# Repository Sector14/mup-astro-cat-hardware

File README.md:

# MUP Astro CAT

The MUP Astro CAT is an auto GPIO configuring add-on board for the
Raspberry PI 3 which provides additional hardware interfaces to 
communicate and control a Meade Autostar, Moonlite focuser and
temperature sensors.

This repository contains the hardware project files needed to build 
the MUP Astro CAT. Firmware and the INDI driver is available in a separte
repo:

  https://github.com/Sector14/mup-astro-cat

Please refer to the additional documentation in the docs/ directory for
information on port pinouts for cables and hardware testing notes.

CAT refers to the Schmidt-Cassagrain telescope (CAT for short) this board will
be attached to. After naming it CAT I considered the recursive "CAP" which
would stand for "CAP Attached on Pi" since this project doesn't quite meet
the "Hat" spec, a cap is not a hat! but that means renaming things so CAT it is.

# Directories

  * control_cat - Kicad 4 project incl schematic/pcb layout for the MUP Astro Cat. (CERN)
  * docs        - Documentation and 3rd party datasheets
  * gerber      - Exported gerber files for re-ordering PCBs

# Intended Purpose

Use a raspberry pi and additional interface board to control the 
following devices:

  * SXVR-H9
  * LodeStar
  * Filter Wheel
  * LX90 Handset
  * Moonlite Focuser
  * Illuminated Reticle (v2?)
  * Temp Sensor

The SXVR-H9, LodeStar (excl ST4 guide port) and Filter Wheel simply 
connect as USB devices to the Pi. 

The LX90 Handset uses a RS232 connection via RJ22 to the PI.

Moonlite focuser controlled via GPIO to a unipolar stepper
motor controller that will handle signal timing. Ensures any 
jitter/pauses from pi due to non realtime OS won't impact
motor control.

ST4 port from APM is not implemented, it might be added in a future
revision via i2c bus however as the LX90 supports pulse commands
over serial, it may not be needed.

# Library Setup

In addition to the libraries, modules and models that ship with Kicad,
this project also uses the MUP Kicad Library for additional parts and
an optional 3rd party 3D model library.

## Eeschema

If you receive a "The following libraries were not found:" message when
opening the schematic then you do not have the MUPS Kicad library available.
Kicad will use a cached copy of the library so this step is optional, but 
if you wish to make changes you should clone the repo:

  https://github.com/Sector14/mup-kicad-library

and add its location "Preferences/Component Libraries" as a user defined 
search path in the "parts library editor".  Then close and re-open Eeschema
and all the schematic symbols should now be found.

## Footprints

The above repo also contains footprint files for PCBNew in the modules/
directory and 3d models (where applicable). PCBNew will need each modules/\*.pretty
directory adding to the global library, or if you prefer, the project specific 
libraries.

To do so, open PCBNew, "Preferences/Footprints Libraries Manager", then 
"Append with Wizard" and select each ".pretty" directory and click Next, then
select whether to add the footprint to the global or project library.

Note: Some footprints are unchanged Kicad footprints that have only been
saved to the MUPS library in order to associate a 3d model with the footprint.
If the official Kicad library ever adds the missing models, the parts will
likely be removed from this repo.

## 3d Models

Some parts include a reference to models from the GPL'd 3d library by "kcswalter".
These are optional models and not included in the MUPS Kicad library.

If you checkout the walter repo from

  git://smisioto.eu/kicad_libs.git 

You can have Kicad use these models during 3d preview mode
by adding a new env variable in PCBNew "Preferences/Configure Paths" 
called WALTER_KI3DMOD and with the path set to the 
<walter repo checkout path>/modules/packages3d/ directory. 

Any footprints in the MUPS library that has the 3d model path prefixed 
with {WALTER_KI3DMOD}/walter/ will then use the appropriate 3D model.
The same will apply to {MUPS_KI3DMOD}/mups/ although at this time I've
yet to create any custom 3D models and find it unlikely I will

# Gerber Export

For Ordering PCBs from dirtypcbs.com

For "plotting":-

  * "Gerber" format is selected.
  * Select Layers F.Cu, B.Cu, F.SilkS, B.Mask, F.Mask, Edge.Cuts
  * Select Options:
   * Plot footprint values
   * Plot footprint references
   * Exclude PCB edge layer from other layers
  * Select Gerber Options:
   * User Protel filename extensions

For Drill file:

  * Units Inches
  * Zeros Format, Suppress leading zeros
  * Drill Map File Format (not used)
  * Drill File Options:
   * Minimal header
   * Merge PTH and NPTH holes into one file
  * Drill origin, Absolute

After export, rename the edge cuts "gm1" extension to "gml" prior
to uploading zip to dirtypcbs.com.

# Future Revision

Selecting surface 1206 style footprint for C8, the 100uF bypass capacitor 
for the DRV8805 was a little costly due to needing higher than 12V. An 
SMD electrolytic would prove significantly cheaper £0.27 vs £2.46
and with a greater voltage margin and not require that much additional 
space for a radial footprint. Lapse in judgement to be corrected on a 
future revision.

The power supply could be reduced in size with a more carefully
selected inductor. Having never laid out a SMPS however, I decided
to stick to the recommended layout and inductors based on the
TI regulator used. Further experimentation will be done prior to
revision 2 along with a change to SMD electrolytics and diodes.

A surface mounting socket to mate the CAT to the pi would be a better
choice as it allows an extended pin leg header to be mounted to the
pi and then the CAT mounted on top. This works out cheaper than the
elevated sockets.

Signal lines all need test point locations making available.

Switch 4p4c and 6p6c connector layout to socket mounting 
to allow panel mount option or in the case of a direct wiring, a
smaller connector area.

USB ideally should also be panel mount but desoldering the PI's
dual sockets is something I'd prefer to avoid.

ST3232 switch to soic version.

Add pin labels to silkscreen for temp port etc current broken square for
ground is too hard to see once a pin header is soldered in place.

Add a via behind the regulator to connect ground planes for better
thermal relief.

HAT specs for back-powering via 5V GPIO header pin requires addition
of an ideal 'safety' diode see [design guide](https://github.com/raspberrypi/hats/blob/master/designguide.md)

# Reference

  * https://github.com/raspberrypi/hats
  * https://github.com/raspberrypi/hats/blob/master/designguide.md
  * https://github.com/xesscorp/RPi_Hat_Template
  * http://www.briandorey.com/post/Raspberry-Pi-3-UART-Boot-Overlay-Part-Two

# Copyright

Copyright Gary Preston 2016.

This documentation describes Open Hardware and is licensed under the
CERN OHL v. 1.2.

You may redistribute and modify this documentation under the terms of the
CERN OHL v.1.2. (http://ohwr.org/cernohl). This documentation is distributed
WITHOUT ANY EXPRESS OR IMPLIED WARRANTY, INCLUDING OF
MERCHANTABILITY, SATISFACTORY QUALITY AND FITNESS FOR A
PARTICULAR PURPOSE. Please see the CERN OHL v.1.2 for applicable
conditions

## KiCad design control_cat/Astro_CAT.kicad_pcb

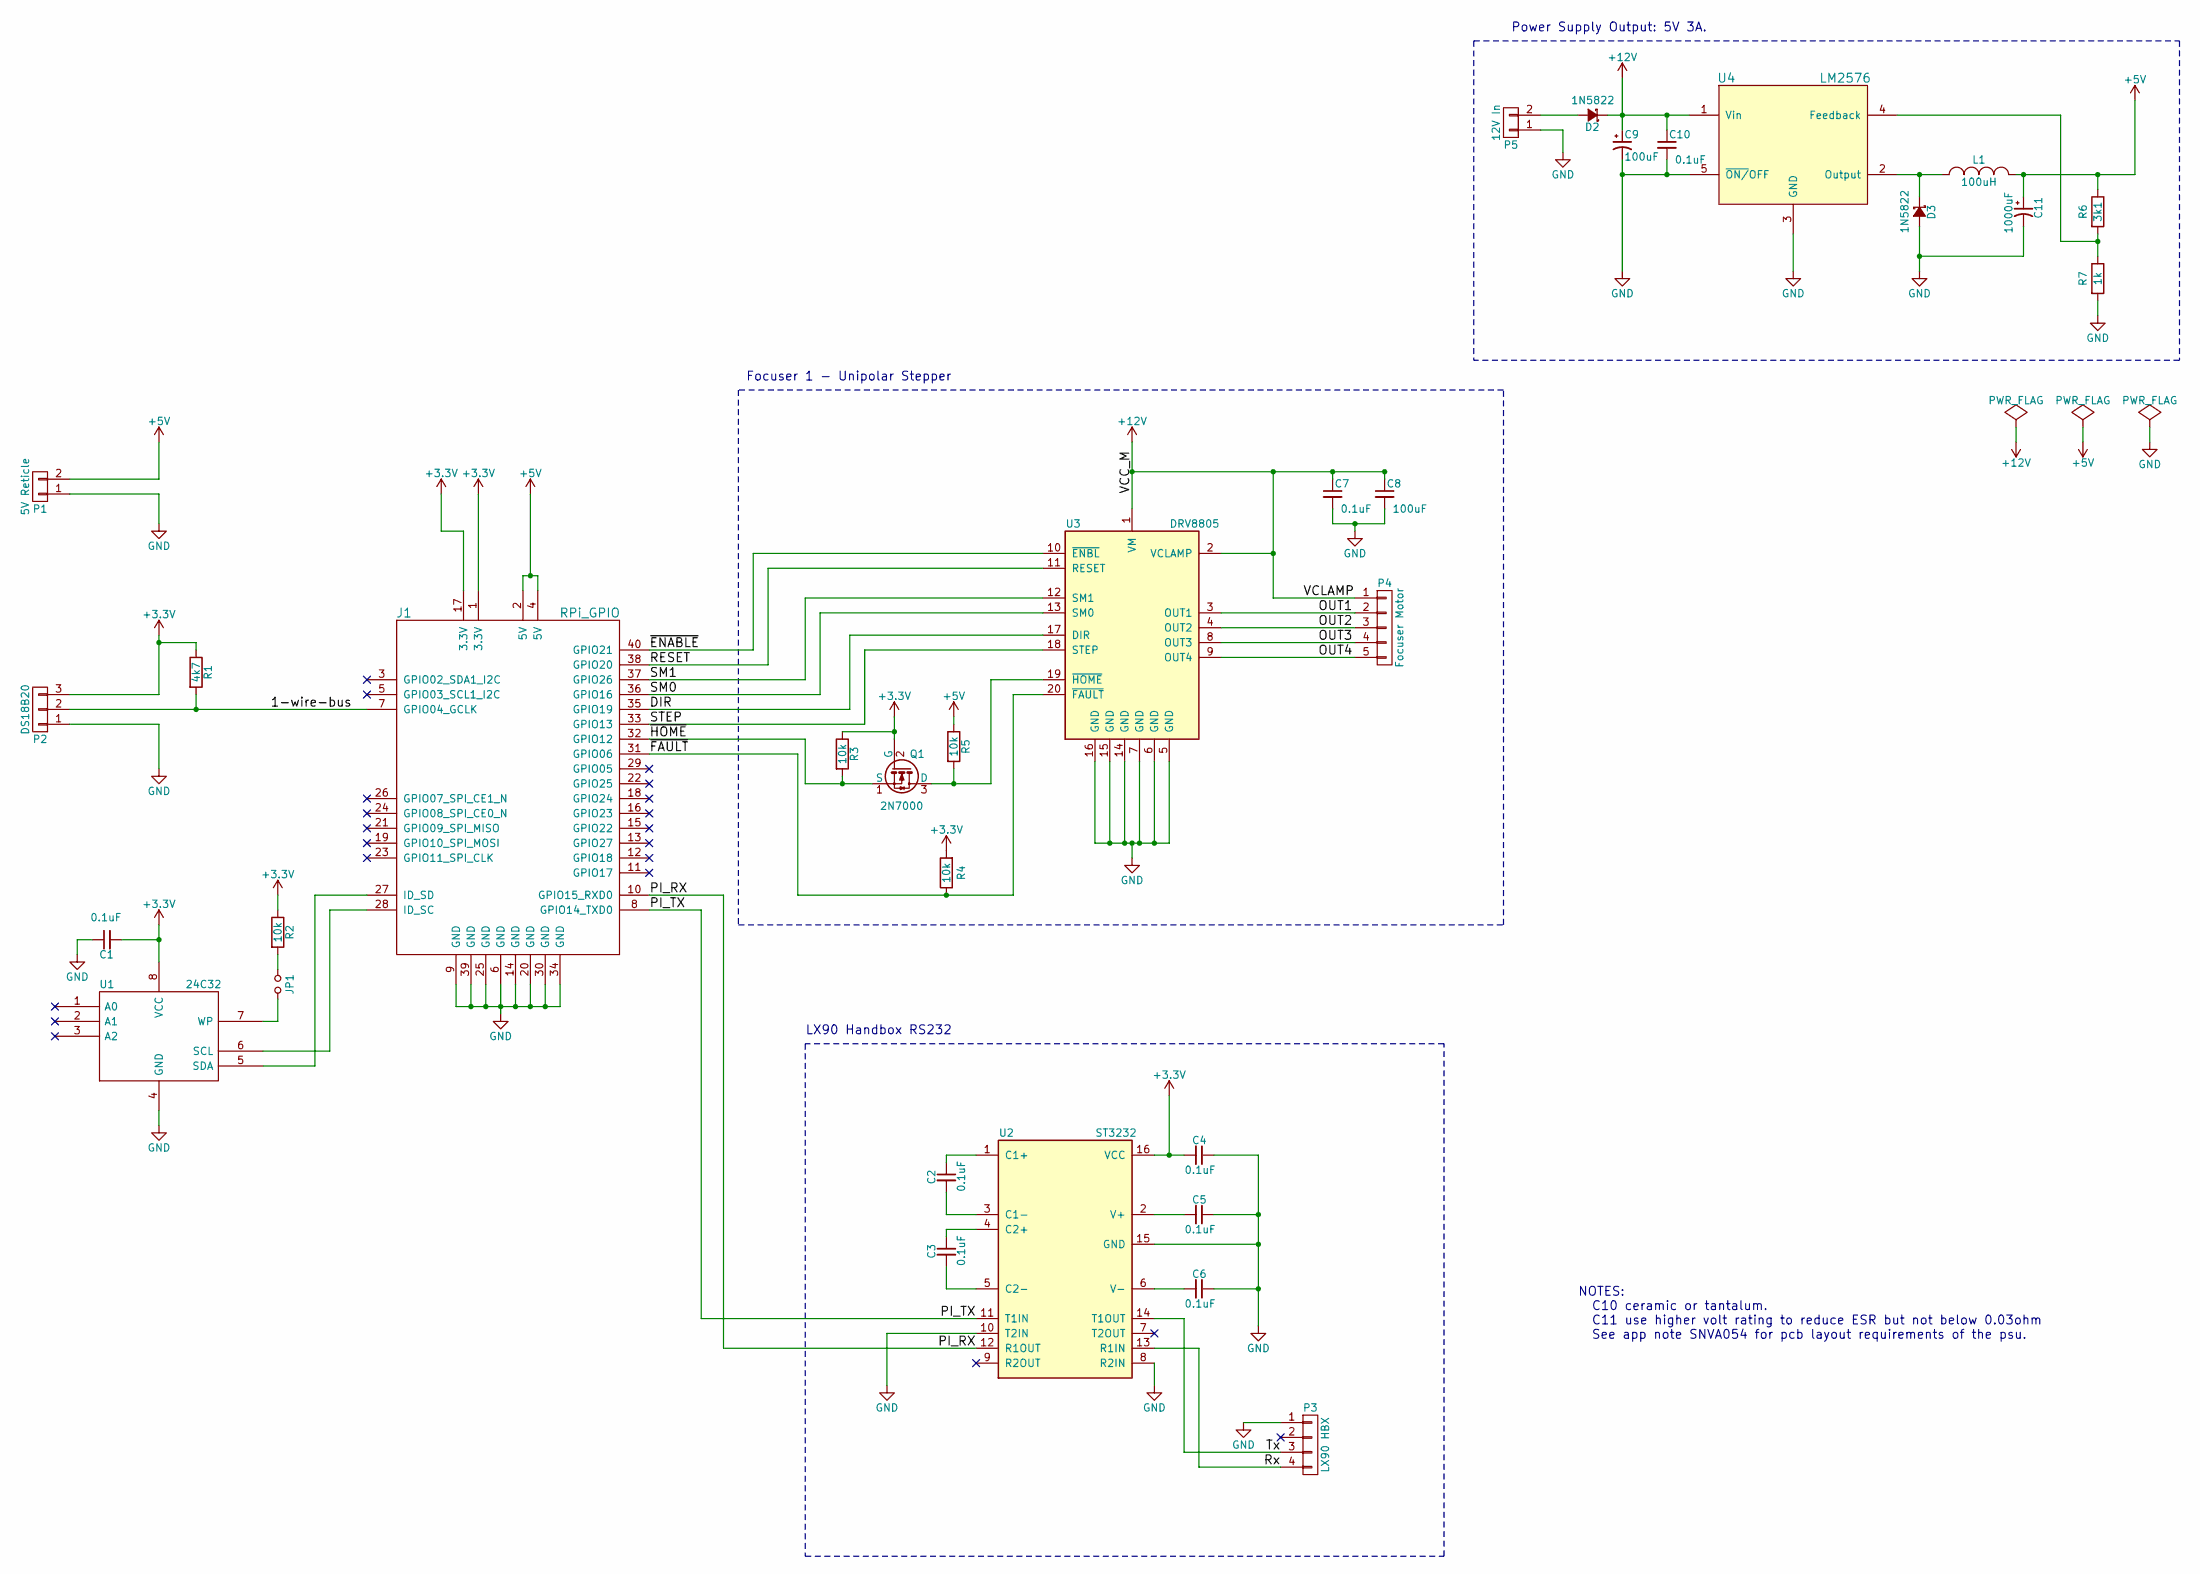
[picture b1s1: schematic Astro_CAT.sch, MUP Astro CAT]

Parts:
C1, C2, C3, C4, C5, C6, C7, C10: 0.1uF; C_1206_HandSoldering
C8: 100uF; C_1206_HandSoldering
C9: 100uF; C_Radial_D6.3_L11.2_P2.5
C11: 1000uF; C_Radial_D10_L16_P5
D2, D3: 1N5822; Diode_DO-201AD_Horizontal_RM15
J1: RPi_GPIO; PI_Pin_Header_Straight_2x20
JP1: Jumper_NO_Small; PINHEAD1-2
L1: 100uH; Choke_Toroid_8x16mm_Vertical
P1: 5V Reticle; Pin_Header_Straight_1x02
P2: DS18B20; Pin_Header_Straight_1x03
P3: LX90 HBX; 4P4C
P4: Focuser Motor; 6P6C
P5: 12V In; Terminal_Block_5mm_2
Q1: 2N7000; TO-92_Inline_Wide
R1: 4k7; R_1206_HandSoldering
R2, R3, R4, R5: 10k; R_1206_HandSoldering
R6: 3k1; R_1206_HandSoldering
R7: 1k; R_1206_HandSoldering
U1: 24C32; SOIC-8_3.9x4.9mm_Pitch1.27mm
U2: ST3232; DIP-16_W7.62mm
U3: DRV8805; SOIC-20_7.5x12.8mm_Pitch1.27mm
U4: LM2576; Pentawatt_Neutral_Staggered_Verical_TO220-5-T05D

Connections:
+3V3: C1.2, C4.2, J1.1 (3.3V), J1.17 (3.3V), P2.3, Q1.2 (G), R1.1, R2.1, R3.1, R4.2, U1.8 (VCC), U2.16 (VCC)
+5V: C11.1, J1.2 (5V), J1.4 (5V), L1.2, P1.2, R5.1, R6.1
+12V: C7.1, C8.1, C9.1, C10.1, D2.1 (K), P4.1, U3.1 (VM), U3.2 (VCLAMP), U4.1 (Vin)
/1-wire-bus: J1.7 (GPIO04_GCLK), P2.2, R1.2
/DIR: J1.35 (GPIO19), U3.17 (DIR)
/OUT1: P4.2, U3.3 (OUT1)
/OUT2: P4.3, U3.4 (OUT2)
/OUT3: P4.4, U3.8 (OUT3)
/OUT4: P4.5, U3.9 (OUT4)
/PI_RX: J1.10 (GPIO15_RXD0), U2.12 (R1OUT)
/PI_TX: J1.8 (GPIO14_TXD0), U2.11 (T1IN)
/RESET: J1.38 (GPIO20), U3.11 (RESET)
/Rx: P3.4, U2.13 (R1IN)
/SM0: J1.36 (GPIO16), U3.13 (SM0)
/SM1: J1.37 (GPIO26), U3.12 (SM1)
/STEP: J1.33 (GPIO13), U3.18 (STEP)
/Tx: P3.3, U2.14 (T1OUT)
/~ENABLE: J1.40 (GPIO21), U3.10 (~ENBL)
/~FAULT: J1.31 (GPIO06), R4.1, U3.20 (~FAULT)
/~HOME: J1.32 (GPIO12), Q1.1 (S), R3.2
GND: C1.1, C4.1, C5.1, C6.1, C7.2, C8.2, C9.2, C10.2, C11.2, D3.2 (A), J1.6 (GND), J1.9 (GND), J1.14 (GND), J1.20 (GND), J1.25 (GND), J1.30 (GND), J1.34 (GND), J1.39 (GND), P1.1, P2.1, P3.1, P5.1, R7.2, U1.4 (GND), U2.8 (R2IN), U2.10 (T2IN), U2.15 (GND), U3.5 (GND), U3.6 (GND), U3.7 (GND), U3.14 (GND), U3.15 (GND), U3.16 (GND), U4.3 (GND), U4.5 (~ON/~OFF)
unnamed: C2.1, U2.1 (C1+)
unnamed: C2.2, U2.3 (C1-)
unnamed: C3.1, U2.4 (C2+)
unnamed: C3.2, U2.5 (C2-)
unnamed: C5.2, U2.2 (V+)
unnamed: C6.2, U2.6 (V-)
unnamed: D2.2 (A), P5.2
unnamed: D3.1 (K), L1.1, U4.2 (Output)
unnamed: J1.27 (ID_SD), U1.5 (SDA)
unnamed: J1.28 (ID_SC), U1.6 (SCL)
unnamed: JP1.1, R2.2
unnamed: JP1.2, U1.7 (WP)
unnamed: Q1.3 (D), R5.2, U3.19 (~HOME)
unnamed: R6.2, R7.1, U4.4 (Feedback)

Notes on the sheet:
LX90 Handbox RS232
Focuser 1 - Unipolar Stepper
Power Supply Output: 5V 3A.
NOTES: C10 ceramic or tantalum. C11 use higher volt rating to reduce ESR but not below 0.03ohm See app note SNVA054 for pcb layout requirements of the psu.

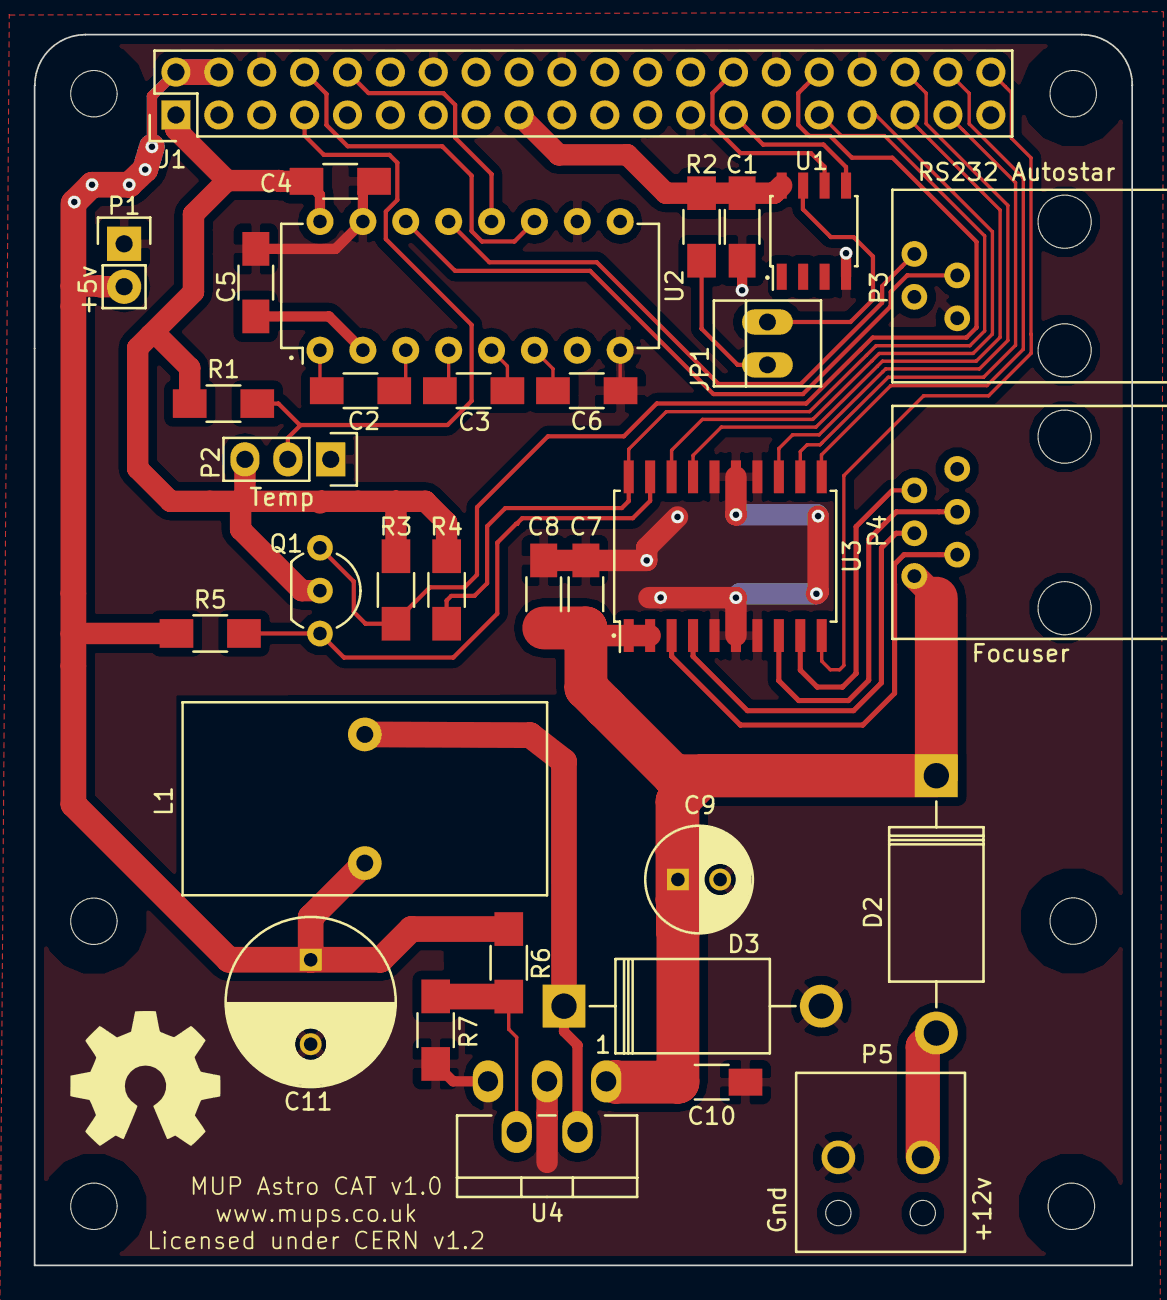
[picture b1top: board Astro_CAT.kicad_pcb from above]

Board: 2 copper layers, 65.0 x 72.9 mm, 33 parts (0 on the bottom side), 35 nets.

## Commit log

2016-11-03 Initial checkin of mup astro hat schematic, pcb and associated reference datasheets.
2016-11-03 Add CERN OHW guide. Adjust wording on schematic. Add v1.0 PDF schematic to docs/ dir.
2016-11-03 Switch footprint pin 1 to 4 around for 4p4c to match 6p6c ordering.
2016-11-11 Update readme with future revision notes.
2016-11-27 Fix voltage divider network r6/r7.
2016-11-28 Switch Q1 to specific component.
    Q1 switched to custom 2N7000 component with gate as pin 2 and S/D to match TO-92 1,2,3 pin ordering of actual package/footprint.
    Update PCB layout with gate (3.3v) now center pin.
2016-12-07 Swap labels for SM0 and SM1 on pi pin side.
2016-12-08 Update readme with kicad repo info and tweaked test script.
2016-12-08 Adjust markdown for bitbucket rendering
2016-12-10 Split docs. Add device overlay and eeprom settings.
2016-12-10 Rename Hat to CAT.
    Due to lack of back powering protection diode and board not meeting
    the HAT mechanical spec, renaming the project to CAT to avoid confusion.
2017-01-30 Splitting hardware off to separate repo.
    Update pinout for cables.
2018-05-17 Update readme paths to reflect move to github.
2024-08-08 Note kicad version used for project files.

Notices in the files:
control_cat/Astro_CAT.kicad_pcb:
Licensed under CERN v1.2
